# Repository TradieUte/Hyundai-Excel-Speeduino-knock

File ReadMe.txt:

The KiCad project will need to have the local library paths altered to suit the download location.
Preferences->Manage symbol libraries->Project specific libraries.

Starting the schematic editor without path changes will generate errors. 
Don't save anything until paths are corrected and errors disappear.

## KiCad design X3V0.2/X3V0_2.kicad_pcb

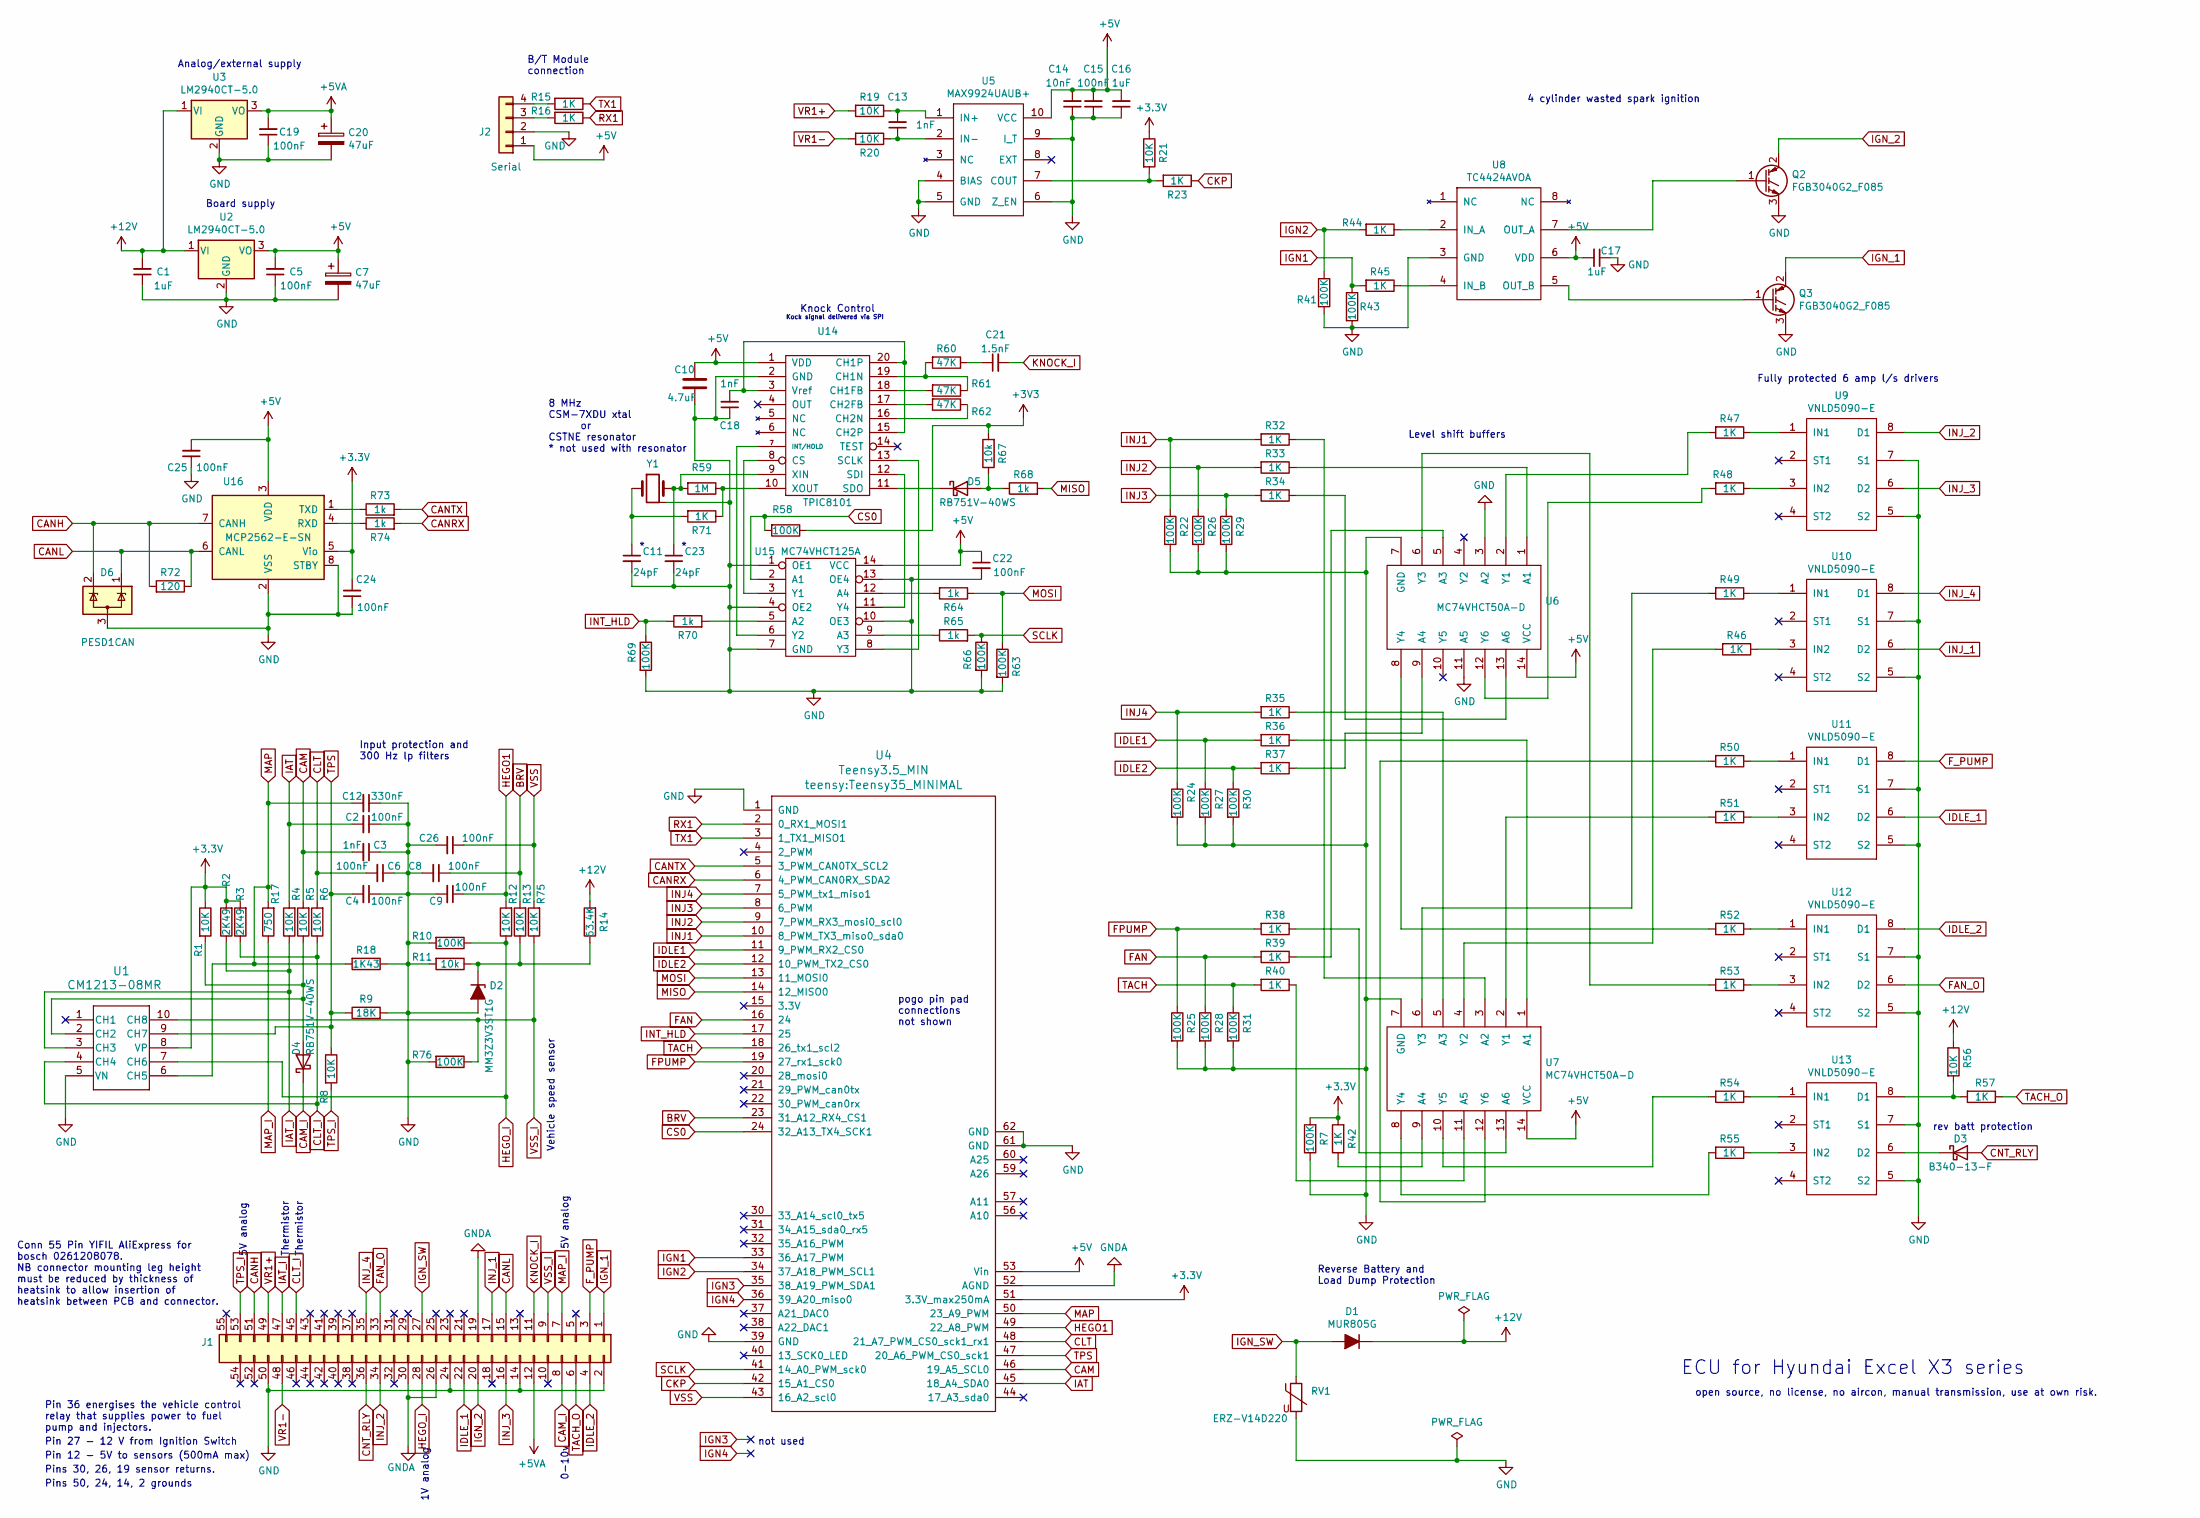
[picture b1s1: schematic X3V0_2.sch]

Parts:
C1, C16, C17: 1uF; C_0805
C2, C4, C5, C6, C8, C9, C15, C19, C22, C24, C25, C26: 100nF; C_0805
C3, C13, C18: 1nF; C_0805
C7, C20: 47uF; CP_Tantalum_Case-B_EIA-3528-21_Reflow
C10: 4.7uF; C_0805
C11, C23: 24pF; C_0805
C12: 330nF; C_0805
C14: 10nF; C_0805
C21: 1.5nF; C_0805
D1: MUR805G; TO-220-2_Vertical
D2: MM3Z3V3ST1G; D_SOD-323
D3: B340-13-F; D_SMC
D4, D5: RB751V-40WS; D_SOD-323F
D6: PESD1CAN; SOT-23
J1: Conn_2Rows-55Pins; Hyundai55
J2: Serial; Pin_Header_Straight_1x04_Pitch2.54mm
Q2, Q3: FGB3040G2_F085; TO-220-3_Vertical_hv
R1, R4, R5, R6, R8, R12, R13, R21, R56, R75: 10K; R_0805
R2, R3: 2K49; R_Axial_DIN0207_L6.3mm_D2.5mm_P10.16mm_Horizontal
R7, R10, R22, R24, R25, R26, R27, R28, R29, R30, R31, R41, R43, R58, R63, R66, R69, R76: 100K; R_0805
R9: 18K; R_0805
R11, R67: 10k; R_0805
R14: 63.4K; R_0805
R15, R16, R23, R32, R33, R34, R35, R36, R37, R38, R39, R40, R42, R44, R45, R46, R47, R48, R49, R50, R51, R52, R53, R54, R55, R57, R71: 1K; R_0805
R17: 750; R_0805
R18: 1K43; R_0805
R19, R20: 10K; R_2512
R59: 1M; R_0805
R60, R61, R62: 47K; R_0805
R64, R65, R68, R70, R73, R74: 1k; R_0805
R72: 120; R_0805
RV1: ERZ-V14D220; RV_Disc_D15.5_W4.8_P7.5
U1: CM1213-08MR
U2, U3: LM2940CT-5.0; TO-220-3_Vertical
U4: Teensy3.5_MIN; Teensy35_MINIMAL
U5: MAX9924UAUB+; MSOP-10_3x3mm_Pitch0.5mm
U6, U7: MC74VHCT50A-D; SOIC-14_3.9x8.7mm_Pitch1.27mm
U8: TC4424AVOA; SOIC-8_3.9x4.9mm_Pitch1.27mm
U9, U10, U11, U12, U13: VNLD5090-E; SOIC-8_3.9x4.9mm_Pitch1.27mm
U14: TPIC8101; SOIC-20W_7.5x12.8mm_Pitch1.27mm
U15: MC74VHCT125A; SOIC-14_3.9x8.7mm_Pitch1.27mm
U16: MCP2562-E-SN; SOIC-8_3.9x4.9mm_Pitch1.27mm
Y1: Crystal_hybrid; Crystal_SMD_HC49-SD_hybrid

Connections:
+5V: C5.2, C7.1, C10.1, C14.2, C15.2, C16.2, C17.2, C22.1, C25.2, J2.1, U2.3 (VO), U4.53 (Vin), U5.10 (VCC), U6.14 (VCC), U7.14 (VCC), U8.6 (VDD), U14.1 (VDD), U15.14 (VCC), U16.3 (VDD)
+5VA: C19.2, C20.1, J1.12, U3.3 (VO)
+12V: C1.2, D1.1 (K), R14.2, R56.1, U2.1 (VI), U3.1 (VI)
BRV: C8.1, R13.2, U4.23 (31_A12_RX4_CS1)
CAM: C3.2, R5.2, U4.46 (19_A5_SCL0)
CAM_I: D4.1 (K), J1.8
CANH: D6.2 (K), J1.51, R72.2, U16.7 (CANH)
CANL: D6.1 (K), J1.15, R72.1, U16.6 (CANL)
CANRX: R74.2, U4.6 (4_PWM_CAN0RX_SDA2)
CANTX: R73.2, U4.5 (3_PWM_CAN0TX_SCL2)
CKP: R23.1, U4.42 (15_A1_CS0)
CLT: C6.2, R6.2, U4.48 (21_A7_PWM_CS0_sck1_rx1)
CLT_I: J1.45, R3.1, R6.1, U1.4 (CH4)
CNT_RLY: D3.2 (A), J1.36
CS0: R58.2, U4.24 (32_A13_TX4_SCK1), U15.2 (A1)
FAN: R28.1, R39.2, U4.16 (24)
FAN_O: J1.33, U12.6 (D2)
FPUMP: R25.1, R38.2, U4.19 (27_rx1_sck0)
F_PUMP: J1.3, U11.8 (D1)
GND: C1.1, C2.1, C3.1, C4.1, C5.1, C6.1, C7.2, C8.2, C9.2, C10.2, C11.2, C12.1, C14.1, C15.1, C16.1, C17.1, C18.1, C19.1, C20.2, C22.2, C23.2, C24.1, C25.1, C26.2, D2.2 (A), D6.3 (A), J1.2, J1.14, J1.24, J1.50, J2.2, Q2.3 (E), Q3.3 (E), R7.1, R9.2, R10.2, R11.2, R18.1, R22.2, R24.2, R25.2, R26.2, R27.2, R28.2, R29.2, R30.2, R31.2, R41.2, R43.2, R63.2, R66.2, R69.2, R76.2, RV1.2, U1.5 (VN), U2.2 (GND), U3.2 (GND), U4.1 (GND), U4.39 (GND), U4.61 (GND), U4.62 (GND), U5.4 (BIAS), U5.5 (GND), U5.6 (Z_EN), U5.9 (I_T), U6.3 (A2), U6.7 (GND), U6.11 (A5), U7.7 (GND), U8.3 (GND), U9.5 (S2), U9.7 (S1), U10.5 (S2), U10.7 (S1), U11.5 (S2), U11.7 (S1), U12.5 (S2), U12.7 (S1), U13.5 (S2), U13.7 (S1), U14.2 (GND), U15.1 (OE1), U15.4 (OE2), U15.7 (GND), U15.10 (OE3), U15.13 (OE4), U16.2 (VSS), U16.8 (STBY), Y1.2 (GND)
GNDA: J1.19, J1.26, J1.30, U4.52 (AGND)
HEGO1: C9.1, R12.2, U4.49 (22_A8_PWM)
HEGO_I: J1.28, R10.1, R12.1, U1.7 (CH6)
IAT: C2.2, R4.2, U4.45 (18_A4_SDA0)
IAT_I: J1.47, R2.1, R4.1, U1.3 (CH3)
IDLE1: R27.1, R36.2, U4.11 (9_PWM_RX2_CS0)
IDLE2: R30.1, R37.2, U4.12 (10_PWM_TX2_CS0)
IDLE_1: J1.22, U11.6 (D2)
IDLE_2: J1.4, U12.8 (D1)
IGN1: R43.1, R45.2, U4.33 (36_A17_PWM)
IGN2: R41.1, R44.2, U4.34 (37_A18_PWM_SCL1)
IGN3: U4.35 (38_A19_PWM_SDA1)
IGN4: U4.36 (39_A20_miso0)
IGN_1: J1.1, Q3.2 (C)
IGN_2: J1.20, Q2.2 (C)
IGN_SW: D1.2 (A), J1.27, RV1.1
INJ1: R22.1, R32.2, U4.10 (8_PWM_TX3_miso0_sda0)
INJ2: R26.1, R33.2, U4.9 (7_PWM_RX3_mosi0_scl0)
INJ3: R29.1, R34.2, U4.8 (6_PWM)
INJ4: R24.1, R35.2, U4.7 (5_PWM_tx1_miso1)
INJ_1: J1.17, U10.6 (D2)
INJ_2: J1.34, U9.8 (D1)
INJ_3: J1.16, U9.6 (D2)
INJ_4: J1.35, U10.8 (D1)
INT_HLD: R69.1, R70.1, U4.17 (25)
KNOCK_I: C21.2, J1.11
MAP: C12.2, R17.2, R18.2, U1.6 (CH5), U4.50 (23_A9_PWM)
MAP_I: J1.7, R17.1
MISO: R68.2, U4.14 (12_MISO0)
MOSI: R63.1, R64.1, U4.13 (11_MOSI0)
unnamed: C11.1, R71.2, Y1.1
unnamed: C13.1, R20.1, U5.2 (IN-)
unnamed: C13.2, R19.1, U5.1 (IN+)
unnamed: C18.2, U14.3 (Vref), U14.15 (CH2P), U14.20 (CH1P)
unnamed: C21.1, R60.1
unnamed: C23.1, R59.2, U14.9 (XIN), Y1.3
unnamed: D2.1 (K), R11.1, R13.1, R14.1
unnamed: D3.1 (K), U13.6 (D2)
unnamed: D4.2 (A), R1.2, R5.1, U1.2 (CH2)
unnamed: D5.1 (K), U14.11 (SDO)
unnamed: D5.2 (A), R67.1, R68.1
unnamed: J2.3, R16.2
unnamed: J2.4, R15.2
unnamed: Q2.1 (G), U8.7 (OUT_A)
unnamed: Q3.1 (G), U8.5 (OUT_B)
unnamed: R21.2, R23.2, U5.7 (COUT)
unnamed: R32.1, U7.3 (A2)
unnamed: R33.1, U6.1 (A1)
unnamed: R34.1, U6.13 (A6)
unnamed: R35.1, U7.5 (A3)
unnamed: R36.1, U7.1 (A1)
unnamed: R37.1, U6.9 (A4)
unnamed: R38.1, U7.13 (A6)
unnamed: R39.1, U6.5 (A3)
unnamed: R40.1, U7.11 (A5)
unnamed: R42.1, U7.9 (A4)
unnamed: R44.1, U8.2 (IN_A)
unnamed: R45.1, U8.4 (IN_B)
unnamed: R46.1, U10.3 (IN2)
unnamed: R46.2, U7.4 (Y2)
unnamed: R47.1, U9.1 (IN1)
unnamed: R47.2, U6.2 (Y1)
unnamed: R48.1, U9.3 (IN2)
unnamed: R48.2, U6.12 (Y6)
unnamed: R49.1, U10.1 (IN1)
unnamed: R49.2, U7.6 (Y3)
unnamed: R50.1, U11.1 (IN1)
unnamed: R50.2, U7.12 (Y6)
unnamed: R51.1, U11.3 (IN2)
unnamed: R51.2, U7.2 (Y1)
unnamed: R52.1, U12.1 (IN1)
unnamed: R52.2, U6.8 (Y4)
unnamed: R53.1, U12.3 (IN2)
unnamed: R53.2, U6.6 (Y3)
unnamed: R54.1, U13.1 (IN1)
unnamed: R54.2, U7.10 (Y5)
unnamed: R55.1, U13.3 (IN2)
unnamed: R55.2, U7.8 (Y4)
unnamed: R56.2, R57.2, U13.8 (D1)
unnamed: R59.1, R71.1, U14.10 (XOUT)
unnamed: R60.2, R61.1, U14.19 (CH1N)
unnamed: R61.2, U14.18 (CH1FB)
unnamed: R62.1, U14.16 (CH2N)
unnamed: R62.2, U14.17 (CH2FB)
unnamed: R64.2, U15.12 (A4)
unnamed: R65.1, U15.9 (A3)
unnamed: R70.2, U15.5 (A2)
unnamed: R73.1, U16.1 (TXD)
unnamed: R74.1, U16.4 (RXD)
unnamed: U14.7 (INT/HOLD), U15.6 (Y2)
unnamed: U14.8 (CS), U15.3 (Y1)
unnamed: U14.12 (SDI), U15.11 (Y4)
unnamed: U14.13 (SCLK), U15.8 (Y3)
RX1: R16.1, U4.2 (0_RX1_MOSI1)
SCLK: R65.2, R66.1, U4.41 (14_A0_PWM_sck0)
TACH: R31.1, R40.2, U4.18 (26_tx1_scl2)
TACH_O: J1.6, R57.1
TPS: C4.2, R8.1, R9.1, U1.9 (CH7), U4.47 (20_A6_PWM_CS0_sck1)
TPS_I: J1.53, R8.2
TX1: R15.1, U4.3 (1_TX1_MISO1)
VR1+: J1.49, R19.2
VR1-: J1.48, R20.2
VSS: C26.1, R75.2, U4.43 (16_A2_scl0)
VSS_I: J1.9, R75.1, R76.1, U1.10 (CH8)

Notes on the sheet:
4 cylinder wasted spark ignition
Input protection and 300 Hz lp filters
Reverse Battery and Load Dump Protection
B/T Module connection
ECU for Hyundai Excel X3 series
open source, no license, no aircon, manual transmission, use at own risk.
Pin 27 - 12 V from Ignition Switch
Pin 12 - 5V to sensors (500mA max)
0-10v
5V analog
Thermistor
1V analog
Level shift buffers
Fully protected 6 amp l/s drivers
Analog/external supply
Board supply
rev batt protection
Pins 30, 26, 19 sensor returns.
Pins 50, 24, 14, 2 grounds
Pin 36 energises the vehicle control relay that supplies power to fuel pump and injectors.
Knock Control
Kock signal delivered via SPI
not used
8 MHz CSM-7XDU xtal or CSTNE resonator * not used with resonator
Conn 55 Pin YIFIL AliExpress for bosch 0261208078. NB connector mounting leg height must be reduced by thickness of heatsink to allow insertion of heatsink between PCB and connector.
pogo pin pad connections not shown
Vehicle speed sensor

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
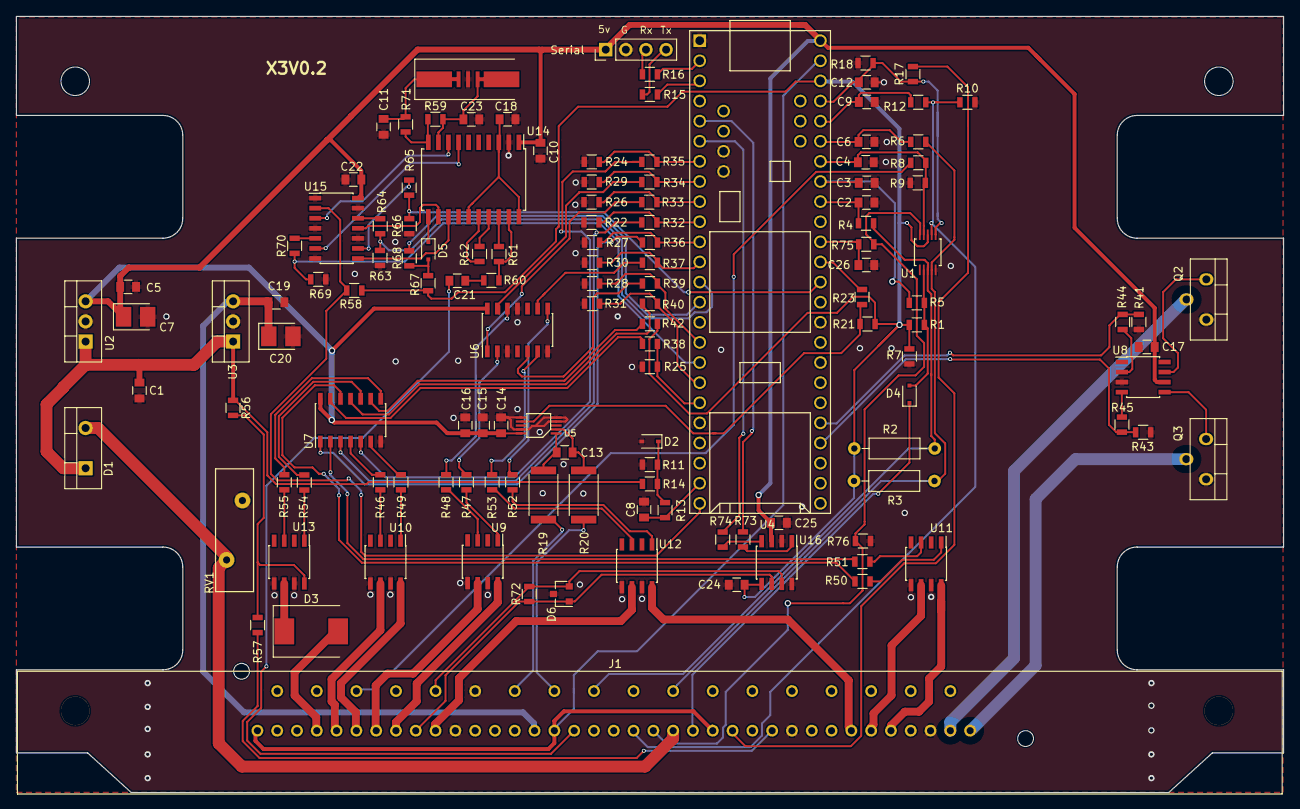
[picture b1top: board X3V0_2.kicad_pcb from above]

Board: 2 copper layers, 160.0 x 98.0 mm, 130 parts (0 on the bottom side), 123 nets.

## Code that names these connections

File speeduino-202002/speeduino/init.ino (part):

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      pinCoil5 = 14; //Pin for coil 5
      pinTrigger = 2; //The CAS pin
      pinTrigger2 = 3; //The CAS pin
      pinTPS = A0; //TPS input pin
      pinMAP = A1; //MAP sensor pin
      pinIAT = A2; //IAT sensor pin
      pinCLT = A3; //CLS sensor pin
      pinO2 = A4; //O2 Sensor pin
      pinIdle1 = 46; //Single wire idle control
      pinIdle2 = 47; //2 wire idle control
      pinStepperDir = 16; //Direction pin  for DRV8825 driver
      pinStepperStep = 17; //Step pin for DRV8825 driver
      pinFan = 47; //Pin for the fan output
      pinFuelPump = 4; //Fuel pump output
      pinTachOut = 49; //Tacho output pin
      pinFlex = 19; // Flex sensor (Must be external interrupt enabled)
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      pinCoil4 = 36; //Pin for coil 4
      pinCoil5 = 34; //Pin for coil 5 PLACEHOLDER value for now
      pinTrigger = 20; //The CAS pin
      pinTrigger2 = 21; //The Cam Sensor pin
      pinTPS = A2; //TPS input pin
      pinMAP = A3; //MAP sensor pin
      pinIAT = A0; //IAT sensor pin
      pinCLT = A1; //CLS sensor pin
      pinO2 = A8; //O2 Sensor pin
      pinBat = A4; //Battery reference voltage pin
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      pinIdle2 = 31; //2 wire idle control
      pinStepperDir = 16; //Direction pin  for DRV8825 driver
      pinStepperStep = 17; //Step pin for DRV8825 driver
      pinFan = 47; //Pin for the fan output
      pinFuelPump = 4; //Fuel pump output
      pinFlex = 2; // Flex sensor (Must be external interrupt enabled)
      pinResetControl = 43; //Reset control output
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      pinCoil4 = 36; //Pin for coil 4
      pinCoil5 = 34; //Pin for coil 5 PLACEHOLDER value for now
      pinTrigger = 19; //The CAS pin
      pinTrigger2 = 18; //The Cam Sensor pin
      pinTPS = A2;//TPS input pin
      pinMAP = A3; //MAP sensor pin
      pinIAT = A0; //IAT sensor pin
      pinCLT = A1; //CLS sensor pin
      pinO2 = A8; //O2 Sensor pin
      pinBat = A4; //Battery reference voltage pin
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      pinStepperDir = 16; //Direction pin  for DRV8825 driver
      pinStepperStep = 17; //Step pin for DRV8825 driver
      pinStepperEnable = 26; //Enable pin for DRV8825
      pinFan = A13; //Pin for the fan output
      pinLaunch = 51; //Can be overwritten below
      pinFlex = 2; // Flex sensor (Must be external interrupt enabled)
      pinResetControl = 50; //Reset control output
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      pinCoil4 = 50; //Pin for coil 4
      pinCoil5 = 34; //Pin for coil 5 PLACEHOLDER value for now
      pinTrigger = 19; //The CAS pin
      pinTrigger2 = 18; //The Cam Sensor pin
      pinTPS = A2;//TPS input pin
      pinMAP = A3; //MAP sensor pin
      pinIAT = A0; //IAT sensor pin
      pinCLT = A1; //CLS sensor pin
      pinO2 = A8; //O2 Sensor pin
      pinBat = A4; //Battery reference voltage pin
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      pinStepperDir = 16; //Direction pin  for DRV8825 driver
      pinStepperStep = 17; //Step pin for DRV8825 driver
      pinStepperEnable = 24; //Enable pin for DRV8825
      pinFan = 47; //Pin for the fan output (Goes to ULN2803)
      pinLaunch = 51; //Can be overwritten below
      pinFlex = 2; // Flex sensor (Must be external interrupt enabled)
      pinResetControl = 43; //Reset control output
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        //******************************************
        //******** PORTD CONNECTIONS *************** 
        //******************************************
        /* = PD0; */ //CANRX
        /* = PD1; */ //CANTX
        /* = PD2; */ //(DO NOT USE FOR SPEEDUINO) - SDIO_CMD
        pinCoil1 = PD3; //
        pinCoil2 = PD4; //
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        pinCoil2 = PB8; //Pin for coil 2
        pinCoil3 = PB3; //Pin for coil 3
        pinCoil4 = PA15; //Pin for coil 4
        pinTPS = A2;//TPS input pin
        pinMAP = A3; //MAP sensor pin
        pinIAT = A0; //IAT sensor pin
        pinCLT = A1; //CLS sensor pin
        pinO2 = A8; //O2 Sensor pin
        pinBat = A4; //Battery reference voltage pin
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        //external interrupt enabled pins
        pinFlex = PB1; // Flex sensor (Must be external interrupt enabled)
        pinTrigger = PB0; //The CAS pin
        pinTrigger2 = PB2; //The Cam Sensor pin
      #endif
      break;

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      pinCoil4 = 33; //Pin for coil 4
      pinCoil5 = 34; //Pin for coil 5 PLACEHOLDER value for now
      pinTrigger = 19; //The CAS pin
      pinTrigger2 = 18; //The Cam Sensor pin
      pinTPS = A2;//TPS input pin
      pinMAP = A5; //MAP sensor pin
      pinIAT = A0; //IAT sensor pin
      pinCLT = A1; //CLS sensor pin
      pinO2 = A3; //O2 Sensor pin
      pinBat = A4; //Battery reference voltage pin
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      pinStepperDir = 16; //Direction pin  for DRV8825 driver
      pinStepperStep = 17; //Step pin for DRV8825 driver
      pinStepperEnable = 24;
      pinFan = 41; //Pin for the fan output
      pinLaunch = 12; //Can be overwritten below
      pinFlex = 3; // Flex sensor (Must be external interrupt enabled)
      pinResetControl = 39; //Reset control output
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      pinCoil4 = 33; //Pin for coil 4
      pinCoil5 = 34; //Pin for coil 5 PLACEHOLDER value for now
      pinTrigger = 19; //The CAS pin
      pinTrigger2 = 18; //The Cam Sensor pin
      pinTPS = A2;//TPS input pin
      pinMAP = A5; //MAP sensor pin
      pinIAT = A0; //IAT sensor pin
      pinCLT = A1; //CLS sensor pin
      pinO2 = A3; //O2 Sensor pin
      pinBat = A4; //Battery reference voltage pin
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      pinStepperDir = 16; //Direction pin  for DRV8825 driver
      pinStepperStep = 17; //Step pin for DRV8825 driver
      pinStepperEnable = 24;
      pinFan = 35; //Pin for the fan output
      pinLaunch = 37; //Can be overwritten below
      pinFlex = 3; // Flex sensor (Must be external interrupt enabled)
      pinResetControl = 44; //Reset control output
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      pinCoil4 = 33; //Pin for coil 4
      pinCoil5 = 34; //Pin for coil 5 PLACEHOLDER value for now
      pinTrigger = 19; //The CAS pin
      pinTrigger2 = 18; //The Cam Sensor pin
      pinTPS = A2;//TPS input pin
      pinMAP = A5; //MAP sensor pin
      pinIAT = A0; //IAT sensor pin
      pinCLT = A1; //CLS sensor pin
      pinO2 = A3; //O2 Sensor pin
      pinBat = A4; //Battery reference voltage pin
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      pinFuelPump = 37; //Fuel pump output
      pinStepperDir = 16; //Direction pin  for DRV8825 driver
      pinStepperStep = 17; //Step pin for DRV8825 driver
      pinFan = 35; //Pin for the fan output
      pinLaunch = 12; //Can be overwritten below
      pinFlex = 3; // Flex sensor (Must be external interrupt enabled)
      pinResetControl = 44; //Reset control output
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      pinCoil4 = 40; //Pin for coil 4
      pinCoil5 = 34; //Pin for coil 5 PLACEHOLDER value for now
      pinTrigger = 18; //The CAS pin
      pinTrigger2 = 19; //The Cam Sensor pin
      pinTPS = A2;//TPS input pin
      pinMAP = A3; //MAP sensor pin
      pinMAP2 = A8; //MAP2 sensor pin
      pinIAT = A0; //IAT sensor pin
      pinCLT = A1; //CLS sensor pin
      pinO2 = A4; //O2 Sensor pin
      pinBat = A7; //Battery reference voltage pin
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      pinSpareTemp2 = A5;
      pinTachOut = 41; //Tacho output pin transistori puuttuu 2n2222 tähän ja 1k 12v
      pinFuelPump = 42; //Fuel pump output 2n2222
      pinFan = 47; //Pin for the fan output
      pinTachOut = 49; //Tacho output pin
      pinFlex = 2; // Flex sensor (Must be external interrupt enabled)
      pinResetControl = 26; //Reset control output
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      pinSpareOut5 = 50; //Spare LSD Output 5(digital)
      pinSpareOut6 = 52; //Spare LSD Output 6(digital)
      pinTrigger = 20; //The CAS pin
      pinTrigger2 = 21; //The Cam Sensor pin
      pinSpareTemp2 = A15; //spare Analog input 2
      pinSpareTemp1 = A14; //spare Analog input 1
      pinO2 = A8; //O2 Sensor pin
      pinBat = A4; //Battery reference voltage pin
      pinMAP = A3; //MAP sensor pin
      pinTPS = A2;//TPS input pin
      pinCLT = A1; //CLS sensor pin
      pinIAT = A0; //IAT sensor pin
      pinFan = 47; //Pin for the fan output
      pinFuelPump = 4; //Fuel pump output
      pinTachOut = 49; //Tacho output pin
      pinResetControl = 26; //Reset control output
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      pinCoil4 = 52; //Pin for coil 4
      pinCoil5 = 34; //Pin for coil 5 PLACEHOLDER value for now
      pinTrigger = 19; //The CAS pin
      pinTrigger2 = 18; //The Cam Sensor pin
      pinTrigger3 = 17; // cam sensor 2 pin
      pinTPS = A2;//TPS input pin
      pinMAP = A3; //MAP sensor pin
      pinIAT = A0; //IAT sensor pin
      pinCLT = A1; //CLS sensor pin
      pinO2 = A8; //O2 Sensor pin
      pinO2_2 = A9; //O2 sensor pin (second sensor)
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      pinSpareLOut3 = 49;
      pinSpareLOut4 = 51;
      pinSpareLOut5 = 53;
      pinFan = 47; //Pin for the fan output
    #endif
      break;

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      pinCoil5 = 36; //Pin for coil 5
	  pinCoil6 = 34; //Pin for coil 6
      pinTrigger = 19; //The CAS pin
      pinTrigger2 = 18; //The Cam Sensor pin
      pinTPS = A2;//TPS input pin
      pinMAP = A3; //MAP sensor pin
      pinIAT = A0; //IAT sensor pin
      pinCLT = A1; //CLS sensor pin
      pinO2 = A8; //O2 Sensor pin
      pinBat = A4; //Battery reference voltage pin
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      pinStepperDir = 16; //Stepper valve isn't used with these
      pinStepperStep = 17; //Stepper valve isn't used with these
      pinStepperEnable = 24; //Stepper valve isn't used with these
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
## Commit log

2020-04-09 included pin layout for excel
2020-04-10 added prog running blink; disabled board layout selection in TS
2020-04-15 Added pinIMCC, pinKnockWin, Board definition for Ford Barra, pinLayout to include "Barra"
2020-04-27 Corrected 6 and 8 channel ignition calculations
2020-04-28 enable IMCC
2020-04-28 definitions for inj and ign pins 5-8
2020-04-28 port defs for IMCC; clear DIAG values
2020-04-28 Added new tacho code for CORE_TEENSY; some work on knock
2020-04-29 Modify tacho code to work with standard speeduino.ini
2020-05-18 More knock work
2020-05-20 Added diagnostic
2020-05-23 For CORE_TEENSY -_Enabled PIT; altered oneMsTimer to use PIT0; Added Diag output to Serial3; Added new Tacho code, using PIT1.
2020-05-26 Added Excel docs
2020-05-26 Interim commit. More knock work.
2020-05-26 minor changes
2020-05-26 resolve function not found
2020-05-27 Moved some code from board_teensy35.ini to knock.ini, added #ifdef KNOCK in various files
2020-05-27 knock corrections
2020-05-28 minor changes in knock code
2020-05-29 Minor corrections
2020-05-29 Minor merge fix
2020-05-29 Corrected freeze when knock turned off
2020-06-04 corrected code error
2020-06-04 Interrupts correction
2020-11-20 Added Kicad file
